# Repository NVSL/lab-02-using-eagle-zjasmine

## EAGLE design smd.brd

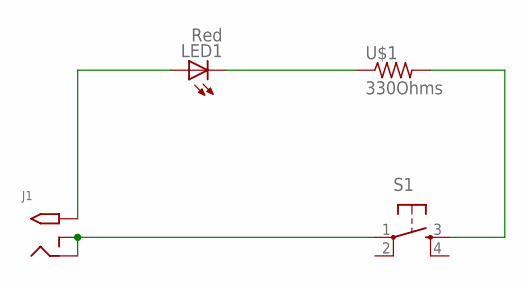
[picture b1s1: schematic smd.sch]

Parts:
J1: 2.1MMJACKTHM; PJ-102A
LED1: Red; LED5MM
S1: BUTTON-TACTILESURFACE_MOUNT; 1301.9315-LSH
U$1: 330Ohms; RESAD1160W55L680D260_HS

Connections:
unnamed: LED1.K (C), U$1.1
unnamed: S1.3 (S), U$1.2
unnamed: J1.RING, J1.RING_SW, S1.1
unnamed: J1.TIP, LED1.A

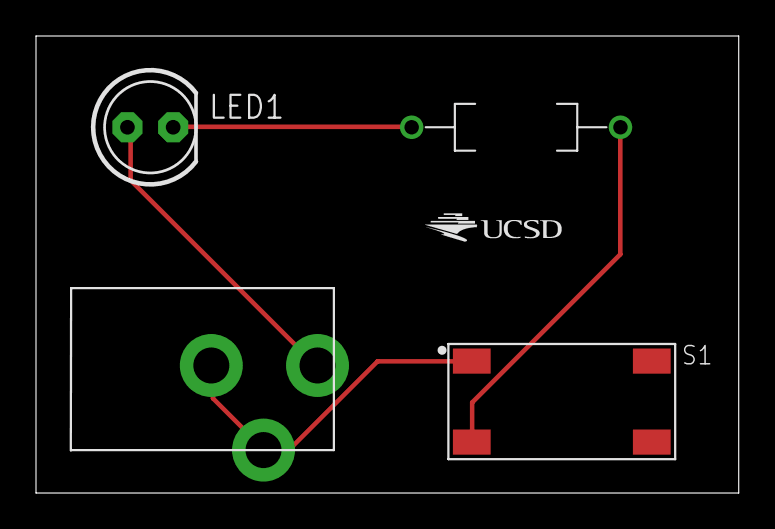
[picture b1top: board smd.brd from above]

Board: 2 copper layers, 39.0 x 25.4 mm, 5 parts (0 on the bottom side), 4 nets.

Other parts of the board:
E$1: UCSD_LOGO

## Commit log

2016-03-17 import from last year
2016-04-07 lab 2 turn-in
